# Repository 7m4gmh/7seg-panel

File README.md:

# 7-Segment LED Panel Video Player

A series of tools for playing videos on a custom display panel composed of I2C-connected 7-segment LED modules.

i2cで駆動する自作の7セグメントLEDパネルで、動画を再生するプロジェクト。

---

Note (platform): Developed and tested primarily on Raspberry Pi 3 and Radxa ROCK 5B. It also works on Raspberry Pi 4/5 if I2C is enabled and dependencies are installed (bus numbers/device names may differ).

**macOS Support**: The project includes emulator mode for macOS development and testing. Physical LED panels are automatically simulated with accurate segment rendering and audio synchronization.

注記（プラットフォーム）: 本プロジェクトは主に Raspberry Pi 3 および Radxa ROCK 5B 向けに作成・検証しています。I2C を有効化し依存関係を整えれば Raspberry Pi 4/5 でも動作します（バス番号やデバイス名が異なる場合があります）。

**macOS対応**: 本プロジェクトはmacOSでの開発・テスト用にエミュレータモードを搭載しています。物理的なLEDパネルを自動的にシミュレートし、正確なセグメント描画と音声同期を実現します。

**Languages:**

[**English**](README.en.md) | [**日本語**](README.ja.md) | [**繁體中文**](README.zh-TW.md)

---

**Module Mapping (モジュールマッピング)**

You can define per-module physical mappings in `config.json` to accommodate different wiring or digit order of hardware modules. Use a simple column-reversal flag (`module_column_reverse`) or an explicit logical→physical index map (`module_index_map`). See `docs/module-mapping.md` for details and examples.

ハードウェア毎に桁順や配線が異なる場合、`config.json` でモジュール単位のマッピングを定義できます。簡易的に列方向を反転する `module_column_reverse`（真偽値）を使うか、論理インデックス（左上から行優先）からモジュール内の物理インデックスへ明示的に変換する `module_index_map`（配列）を定義してください。優先順位は `module_index_map` → `module_column_reverse` → 既定順（row-major）です。詳しい書き方とテスト手順は `docs/module-mapping.md` を参照してください。

実機縮退モデルでのデモ動画

[エミュレータでの実行例](https://x.com/HijiriUmemoto/status/2095140881489899897?s=20)

---

## Hardware (KiCad)

- PCB projects live under `hardware/`. See: [hardware/README.md](hardware/README.md)
- Current folders (subject to change):
	- `hardware/7seg-led` — LED panel PCB
	- `hardware/7seg-control` — main controller PCB
	- `hardware/7seg-hat` — Raspberry Pi HAT
	- `hardware/7seg-power` — power board
	- Shared libs: `hardware/lib`
	- Legacy/migration folders may also exist (e.g., `hardware/led-panel`, `controller`, `rpi-hat`, `power`).

---
## Build

Prerequisites
- C++17-capable compiler (g++)
- make
- OpenCV 4 (dev package)
- SDL2 (dev package)
- GStreamer 1.0 (for RTP/HTTP streaming tools)

How to build
- By default, running `make` without arguments shows help and does not build anything.
- Use the grouped targets below as needed.

Common targets

```bash

# Show available targets (default)

make core

# GStreamer-based tools: http-streamer / rtp-player
make gst

# Individual targets
make rtp        # 7seg-rtp-player
# (http-streamerは削除済み)

# Everything
make all

# Cleanup
### macOS Emulator Support
The project includes macOS emulator support for development and testing without physical hardware:
- Automatically detects macOS and uses emulator mode
- Physical LED panel simulation with accurate segment shapes
- Optimized performance with pre-cached layouts
- Audio synchronization for smooth playback

**macOSでのビルド:**
```bash
# OpenCVのインストール
brew install opencv

# ビルド
make core

# エミュレータでのテスト
./7seg-file-player test.mp4 emulator-24x4
```

## Recent changes (video scaling behavior)

This project recently received fixes and improvements to the video scaling modes so behavior is consistent across orientations (horizontal/vertical) and between the real-device and emulator playback paths.

- FIT (default): the entire video is scaled to fit inside the display's physical aspect ratio. Black padding (letterboxing/pillarboxing) will be added on the shorter axis. Internally we compute a display-shaped ROI based on the configured module layout and physical character dimensions, scale the source to fit into that ROI, and pass only the ROI downstream for sampling. This prevents accidental cropping or distortion.

- CROP: the video is center-cropped to match the display's physical aspect ratio while preserving the source aspect ratio. After cropping the ROI is passed downstream without forcing a full W×H canvas resize, so the sampled region keeps correct proportions.

- STRETCH: the video is resized non-uniformly to fill the display-shaped ROI (i.e. aspect ratio is not preserved). This intentionally distorts the video to use the full display area.

These changes make the three modes behave predictably for combinations like horizontal video on vertical displays (FIT will letterbox, CROP will center-crop, STRETCH will distort to fill).

## Debug logging

A new runtime flag is available to enable extra debug output for scaling and ROI calculation.

Usage:
```bash
# Enable debug output
./bin/darwin-arm64/7seg-file-player <video> <config> --fit --debug

# Short form
./bin/darwin-arm64/7seg-file-player <video> <config> --fit -d
```

When enabled the player prints per-frame messages like:

- [FIT] source_aspect=... display_aspect=... roi=(x,y,w,h) dst=(w,h)
- [STRETCH] source_aspect=... display_aspect=... roi=(x,y,w,h)

The debug flag is off by default so normal runs are quiet.

## Notes for reviewers / maintainers

- The playback code now avoids forcing a W×H resize for FIT/CROP/STRETCH; we pass an appropriately-shaped ROI to the sampling logic so `frame_to_grid` sees the correct proportions.
- Debug prints are gated by the `--debug`/`-d` switch.
- Some small cleanups were applied (unused variables removed, minor refactor of logging points).

Tip
- For streaming, we recommend the net player with OBS via FLV/TCP:
	- [README.en.md](README.en.md) → "Send directly from OBS (FLV/TCP)"
	- [README.ja.md](README.ja.md) → 「OBSから直接送信（FLV/TCP）」
	- [README.zh-TW.md](README.zh-TW.md) → 「從 OBS 直接傳送（FLV/TCP）」
- Alternatively, the RTP player is available. See usage and sender examples:
	- [README.en.md](README.en.md) → "RTP Player (Recommended)"
	- [README.ja.md](README.ja.md) → 「RTPプレイヤー（推奨）」
	- [README.zh-TW.md](README.zh-TW.md) → 「RTP 播放器（建議）」
- macOS camera sender script included: `send_rtp_cam_gst.sh`
 - For browser-based control and uploads, use the HTTP player/streamer. See:
	 - [README.en.md](README.en.md) → "HTTP Player"
	 - [README.ja.md](README.ja.md) → 「HTTPプレイヤー」
	 - [README.zh-TW.md](README.zh-TW.md) → 「HTTP 播放器」
 - To play a local video file quickly, use the File Player. See:
	 - [README.en.md](README.en.md) → "File Player"
	 - [README.ja.md](README.ja.md) → 「ファイルプレイヤー」
	 - [README.zh-TW.md](README.zh-TW.md) → 「檔案播放器」

- **macOS Emulator**: For testing and development on macOS without physical hardware. See:
	 - [README.emulator.md](README.emulator.md) → "7-Segment LED Panel Emulator"
	 - 物理的なLEDパネルの正確なシミュレーション
	 - 動画ファイルからの再生と音声同期

- Tetris on the LED panel (Python):
	- [README.tetris.en.md](README.tetris.en.md)
	- [README.tetris.md](README.tetris.md)（日本語）
	- [README.tetris.zh-TW.md](README.tetris.zh-TW.md)

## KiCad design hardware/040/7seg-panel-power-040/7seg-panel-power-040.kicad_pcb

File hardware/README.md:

# Hardware projects

基板ごとに独立した KiCad プロジェクトとして、世代・構成別のフォルダに配置しています。

This folder contains independent KiCad projects grouped by hardware generation and configuration.

## Directory structure

### 040 series

- `040/`
    - `7seg-panel-control-040/`
    - `7seg-panel-control-040-dual/`
    - `7seg-panel-control-040-single/`
    - `7seg-panel-control-04in/`
    - `7seg-panel-display-040-dual/`
    - `7seg-panel-display-040-dual-24x16/`
    - `7seg-panel-expand-040/`
    - `7seg-panel-power-040/`
    - `7seg-panel-single-04in/`
- `040-sparse/`
    - `7seg-panel-040-display-dual-wide/`
    - `7seg-panel-040-dual-combined-sparse/`

### 056 series

- `056/`
    - `7seg-control/`
    - `7seg-led/`
    - `7seg-panel-4digit/`
    - `7seg-panel-single-digit/`
    - `7seg-power/`
- `056-sparse/`
    - `7-seg-panel-0560dual combined-sparse/`
    - `7seg-panel-056-display-wide/`
    - `7seg-panel-056-single-combined-sparse/`
- `056-HT1635D/`
    - `056-ht1635d-driver/`

### Raspberry Pi HAT

- `7seg-hat/`
    - `7seg-hat.kicad_pro`, `7seg-hat.kicad_sch`, `7seg-hat.kicad_pcb`
    - `7seg-hat-backups/`
    - `20250729-7seg-led-panel-hat-backups/`
    - `20250815-7seg-led-panel-hat-backups/`
    - `bom/`
    - `production/`

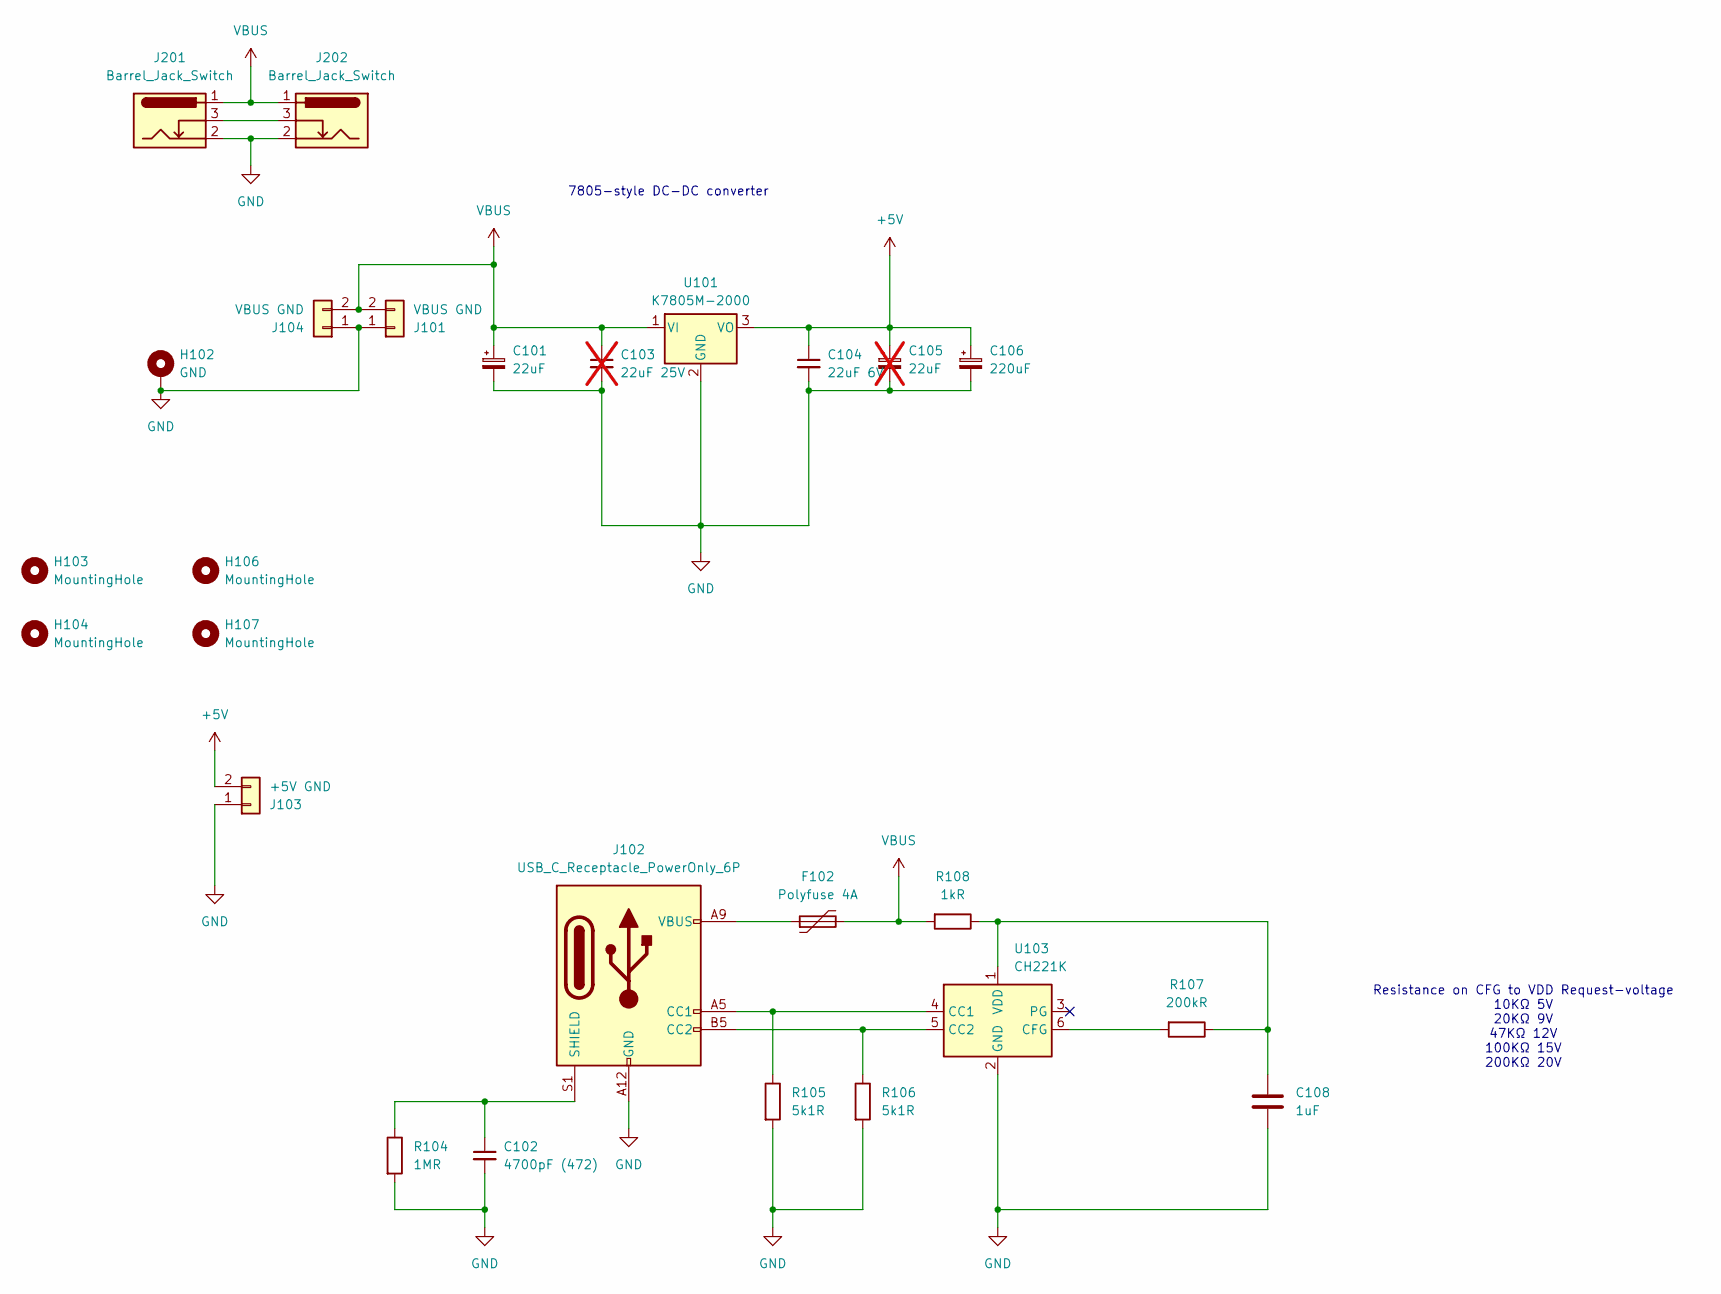
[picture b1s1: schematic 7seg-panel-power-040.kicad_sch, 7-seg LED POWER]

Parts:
C101: 22uF; CP_EIA-3528-21_Kemet-B
C102: 4700pF (472); C_0805_2012Metric_Pad1.18x1.45mm_HandSolder
C103: 22uF 25V; C_0603_1608Metric_Pad1.08x0.95mm_HandSolder; not fitted
C104: 22uF 6V; C_0603_1608Metric_Pad1.08x0.95mm_HandSolder
C105: 22uF; CP_EIA-3528-21_Kemet-B; not fitted
C106: 220uF; CP_Radial_D6.3mm_P2.50mm
C108: 1uF; C_0805_2012Metric_Pad1.18x1.45mm_HandSolder
F102: Polyfuse 4A; Fuse_2920_7451Metric_Pad2.10x5.45mm_HandSolder
H102: GND; MountingHole_3.2mm_M3_DIN965_Pad
H103, H104, H106, H107: MountingHole; MountingHole_3.2mm_M3
J101, J104: VBUS GND; Generic_XH_S2B-XH-A-1_1x02_P2.50mm_Horizontal
J102: USB_C_Receptacle_PowerOnly_6P; USB_C_Receptacle_HRO_TYPE-C-31-M-17
J103: +5V GND; Generic_XH_S2B-XH-A-1_1x02_P2.50mm_Horizontal
J201, J202: Barrel_Jack_Switch; BarrelJack_Singatron_2DC-0415D200-SMT_Horizontal
R104: 1MR; R_0805_2012Metric_Pad1.20x1.40mm_HandSolder
R105, R106: 5k1R; R_0805_2012Metric_Pad1.20x1.40mm_HandSolder
R107: 200kR; R_0805_2012Metric_Pad1.20x1.40mm_HandSolder
R108: 1kR; R_1210_3225Metric_Pad1.30x2.65mm_HandSolder
U101: K7805M-2000; TO-220-3_Vertical
U103: CH221K; TSOT-23-6_HandSoldering

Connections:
+5V: C104.1, C105.1, C106.1, J103.2, U101.3 (VO)
GND: C101.2, C102.2, C103.2, C104.2, C105.2, C106.2, C108.2, H102.1 (MP_1), J101.1, J102.A12 (GND), J102.B12 (GND), J103.1, J104.1, J201.2, J202.2, R104.2, R105.2, R106.2, U101.2 (GND), U103.2 (GND)
unnamed: F102.1, J102.A9 (VBUS), J102.B9 (VBUS)
unnamed: J102.A5 (CC1), R105.1, U103.4 (CC1)
unnamed: J102.B5 (CC2), R106.1, U103.5 (CC2)
unnamed: C102.1, J102.S1 (SHIELD), R104.1
unnamed: J201.3, J202.3
unnamed: R107.2, U103.6 (CFG)
unnamed: C108.1, R107.1, R108.1, U103.1 (VDD)
VBUS: C101.1, C103.1, F102.2, J101.2, J104.2, J201.1, J202.1, R108.2, U101.1 (VI)

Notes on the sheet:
7805-style DC-DC converter
Resistance on CFG to VDD Request-voltage 10KΩ 5V 20KΩ 9V 47KΩ 12V 100KΩ 15V 200KΩ 20V

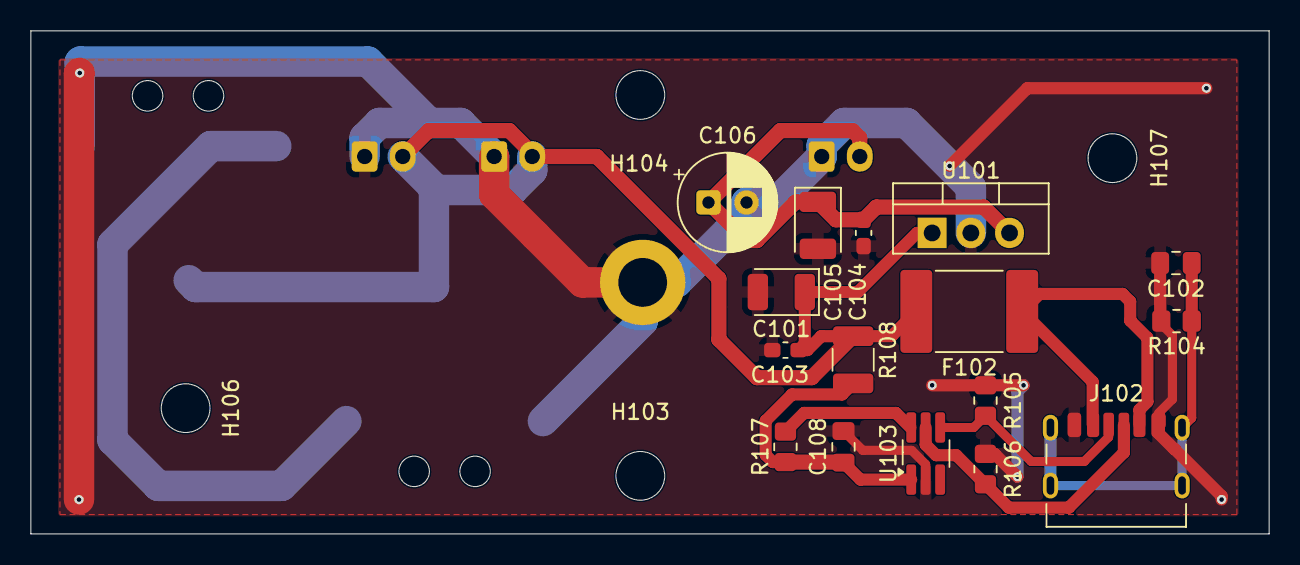
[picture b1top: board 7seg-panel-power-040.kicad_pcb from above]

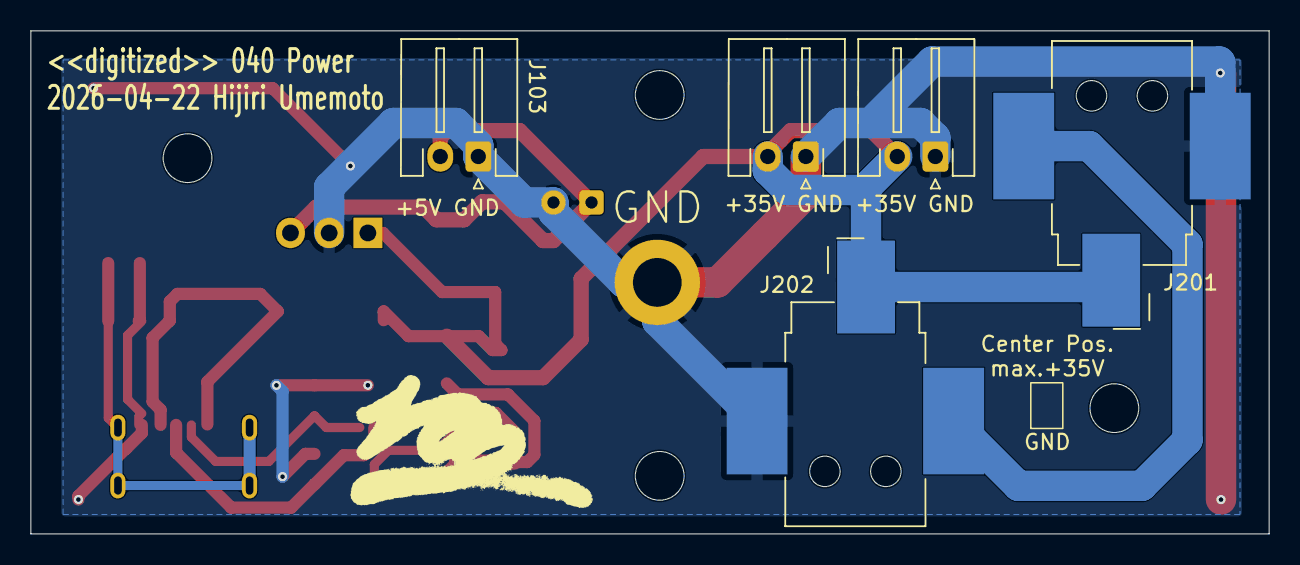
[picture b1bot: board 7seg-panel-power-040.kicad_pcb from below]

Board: 2 copper layers, 81.3 x 33.0 mm, 26 parts (5 on the bottom side), 10 nets.

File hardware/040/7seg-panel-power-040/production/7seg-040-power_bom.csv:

Designator,Footprint,Quantity,Value,LCSC Part #
C101,CP_EIA-3528-21_Kemet-B,1,22uF,
C102,0805,1,4700pF (472),
C104,0603,1,22uF 6V,
C106,CP_Radial_D6.3mm_P2.50mm,1,220uF,
C108,0805,1,1uF,
F102,2920,1,Polyfuse 4A,
"J101, J104",Generic_XH_S2B-XH-A-1_1x02_P2.50mm_Horizontal,2,+35V GND,
J102,USB_C_Receptacle_HRO_TYPE-C-31-M-17,1,USB_C_Receptacle_PowerOnly_6P,
J103,Generic_XH_S2B-XH-A-1_1x02_P2.50mm_Horizontal,1,+5V GND,
"J201, J202",BarrelJack_Singatron_2DC-0415D200-SMT_Horizontal,2,Barrel_Jack_Switch,
R104,0805,1,1MR,
"R105, R106",0805,2,5k1R,
R107,0805,1,200kR,
R108,1210,1,1kR,
U101,TO-220-3_Vertical,1,K7805M-2000,
U103,TSOT-23-6_HandSoldering,1,CH221K,

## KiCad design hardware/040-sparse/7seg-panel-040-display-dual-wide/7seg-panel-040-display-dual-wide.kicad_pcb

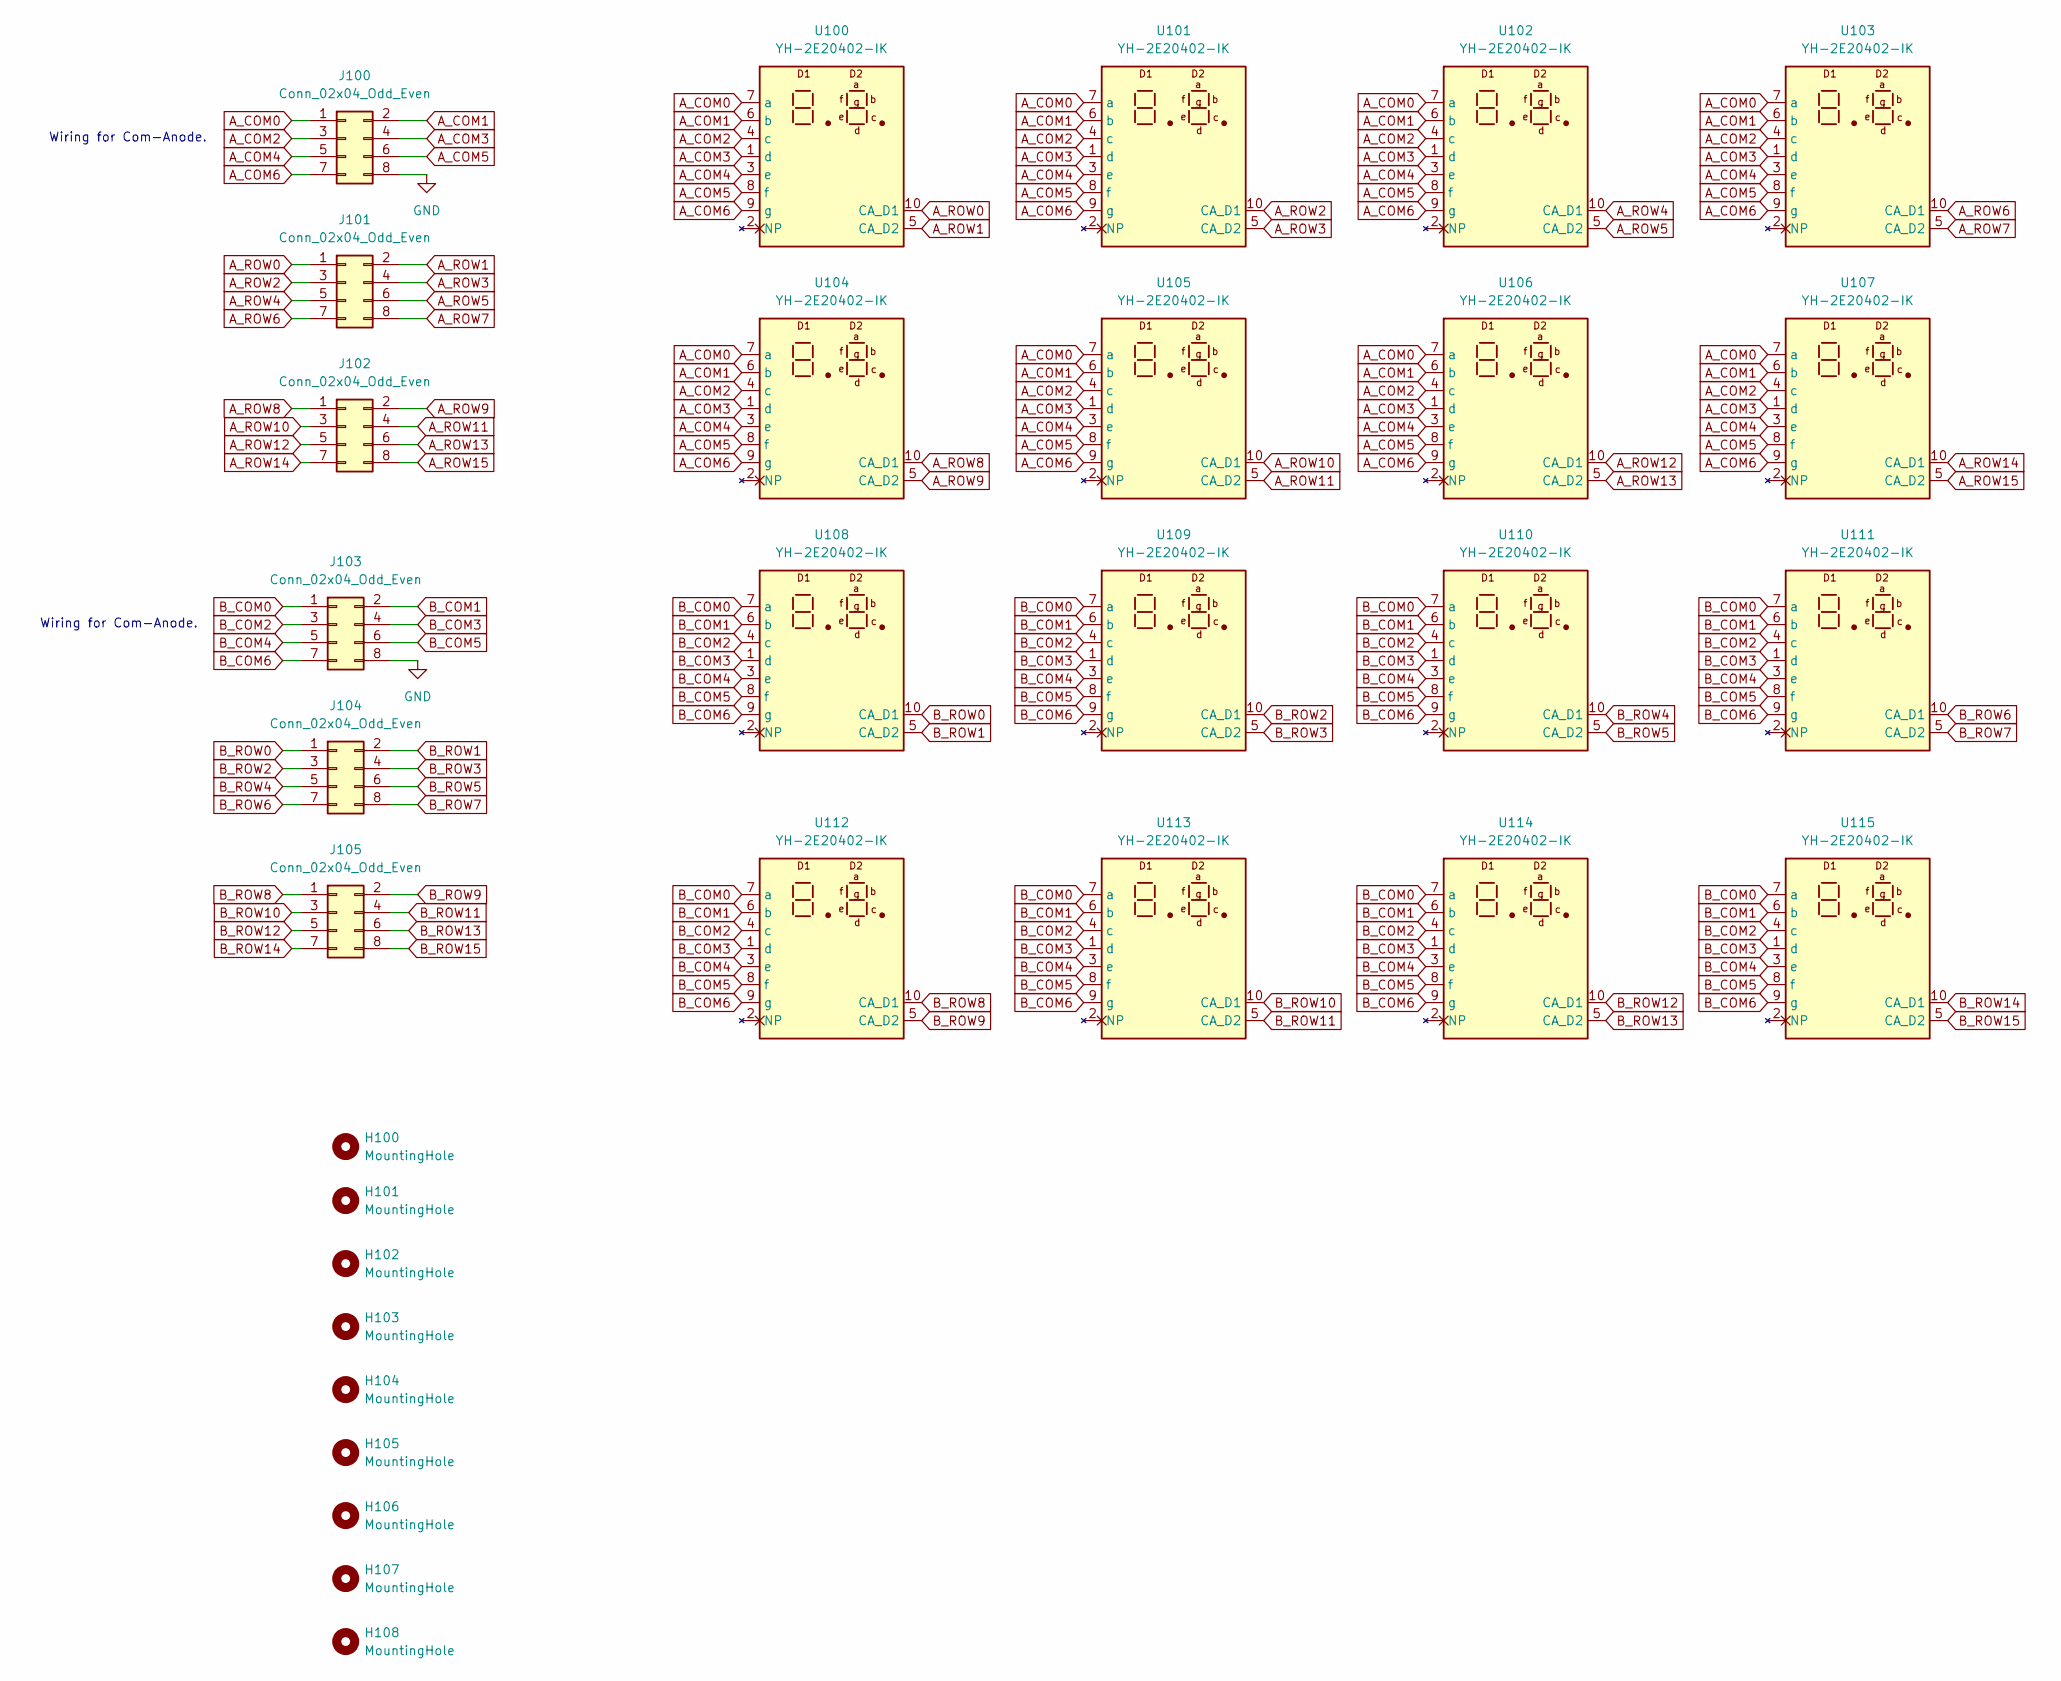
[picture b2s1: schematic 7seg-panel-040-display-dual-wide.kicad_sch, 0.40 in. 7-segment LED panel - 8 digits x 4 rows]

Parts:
H100, H101, H102, H103, H104, H105, H106, H107, H108: MountingHole; MountingHole_3.2mm_M3
J100, J101, J102, J103, J104, J105: Conn_02x04_Odd_Even; PinHeader_2x04_P2.54mm_Vertical
U100, U101, U102, U103, U104, U105, U106, U107, U108, U109, U110, U111, U112, U113, U114, U115: YH-2E20402-IK; YH-2E20402-12P

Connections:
A_COM0: J100.1, U100.7 (a), U101.7 (a), U102.7 (a), U103.7 (a), U104.7 (a), U105.7 (a), U106.7 (a), U107.7 (a)
A_COM1: J100.2, U100.6 (b), U101.6 (b), U102.6 (b), U103.6 (b), U104.6 (b), U105.6 (b), U106.6 (b), U107.6 (b)
A_COM2: J100.3, U100.4 (c), U101.4 (c), U102.4 (c), U103.4 (c), U104.4 (c), U105.4 (c), U106.4 (c), U107.4 (c)
A_COM3: J100.4, U100.1 (d), U101.1 (d), U102.1 (d), U103.1 (d), U104.1 (d), U105.1 (d), U106.1 (d), U107.1 (d)
A_COM4: J100.5, U100.3 (e), U101.3 (e), U102.3 (e), U103.3 (e), U104.3 (e), U105.3 (e), U106.3 (e), U107.3 (e)
A_COM5: J100.6, U100.8 (f), U101.8 (f), U102.8 (f), U103.8 (f), U104.8 (f), U105.8 (f), U106.8 (f), U107.8 (f)
A_COM6: J100.7, U100.9 (g), U101.9 (g), U102.9 (g), U103.9 (g), U104.9 (g), U105.9 (g), U106.9 (g), U107.9 (g)
A_ROW0: J101.1, U100.10 (CA_D1)
A_ROW1: J101.2, U100.5 (CA_D2)
A_ROW2: J101.3, U101.10 (CA_D1)
A_ROW3: J101.4, U101.5 (CA_D2)
A_ROW4: J101.5, U102.10 (CA_D1)
A_ROW5: J101.6, U102.5 (CA_D2)
A_ROW6: J101.7, U103.10 (CA_D1)
A_ROW7: J101.8, U103.5 (CA_D2)
A_ROW8: J102.1, U104.10 (CA_D1)
A_ROW9: J102.2, U104.5 (CA_D2)
A_ROW10: J102.3, U105.10 (CA_D1)
A_ROW11: J102.4, U105.5 (CA_D2)
A_ROW12: J102.5, U106.10 (CA_D1)
A_ROW13: J102.6, U106.5 (CA_D2)
A_ROW14: J102.7, U107.10 (CA_D1)
A_ROW15: J102.8, U107.5 (CA_D2)
B_COM0: J103.1, U108.7 (a), U109.7 (a), U110.7 (a), U111.7 (a), U112.7 (a), U113.7 (a), U114.7 (a), U115.7 (a)
B_COM1: J103.2, U108.6 (b), U109.6 (b), U110.6 (b), U111.6 (b), U112.6 (b), U113.6 (b), U114.6 (b), U115.6 (b)
B_COM2: J103.3, U108.4 (c), U109.4 (c), U110.4 (c), U111.4 (c), U112.4 (c), U113.4 (c), U114.4 (c), U115.4 (c)
B_COM3: J103.4, U108.1 (d), U109.1 (d), U110.1 (d), U111.1 (d), U112.1 (d), U113.1 (d), U114.1 (d), U115.1 (d)
B_COM4: J103.5, U108.3 (e), U109.3 (e), U110.3 (e), U111.3 (e), U112.3 (e), U113.3 (e), U114.3 (e), U115.3 (e)
B_COM5: J103.6, U108.8 (f), U109.8 (f), U110.8 (f), U111.8 (f), U112.8 (f), U113.8 (f), U114.8 (f), U115.8 (f)
B_COM6: J103.7, U108.9 (g), U109.9 (g), U110.9 (g), U111.9 (g), U112.9 (g), U113.9 (g), U114.9 (g), U115.9 (g)
B_ROW0: J104.1, U108.10 (CA_D1)
B_ROW1: J104.2, U108.5 (CA_D2)
B_ROW2: J104.3, U109.10 (CA_D1)
B_ROW3: J104.4, U109.5 (CA_D2)
B_ROW4: J104.5, U110.10 (CA_D1)
B_ROW5: J104.6, U110.5 (CA_D2)
B_ROW6: J104.7, U111.10 (CA_D1)
B_ROW7: J104.8, U111.5 (CA_D2)
B_ROW8: J105.1, U112.10 (CA_D1)
B_ROW9: J105.2, U112.5 (CA_D2)
B_ROW10: J105.3, U113.10 (CA_D1)
B_ROW11: J105.4, U113.5 (CA_D2)
B_ROW12: J105.5, U114.10 (CA_D1)
B_ROW13: J105.6, U114.5 (CA_D2)
B_ROW14: J105.7, U115.10 (CA_D1)
B_ROW15: J105.8, U115.5 (CA_D2)
GND: J100.8, J103.8

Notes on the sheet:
Wiring for Com-Anode.

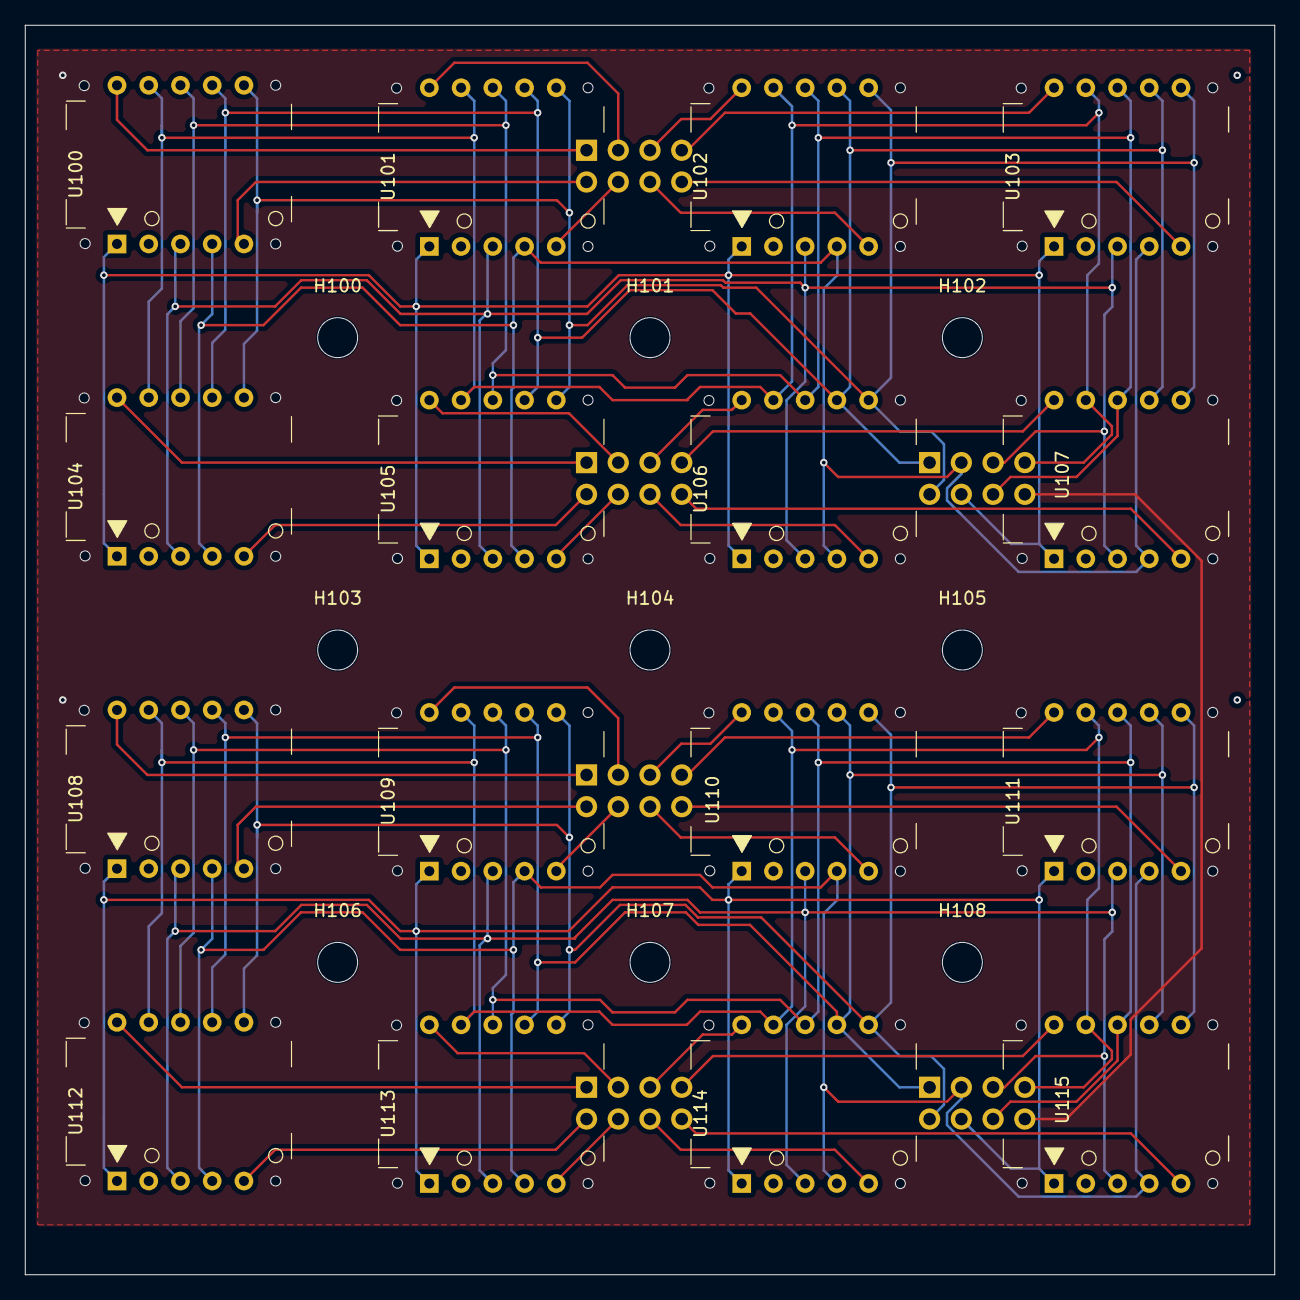
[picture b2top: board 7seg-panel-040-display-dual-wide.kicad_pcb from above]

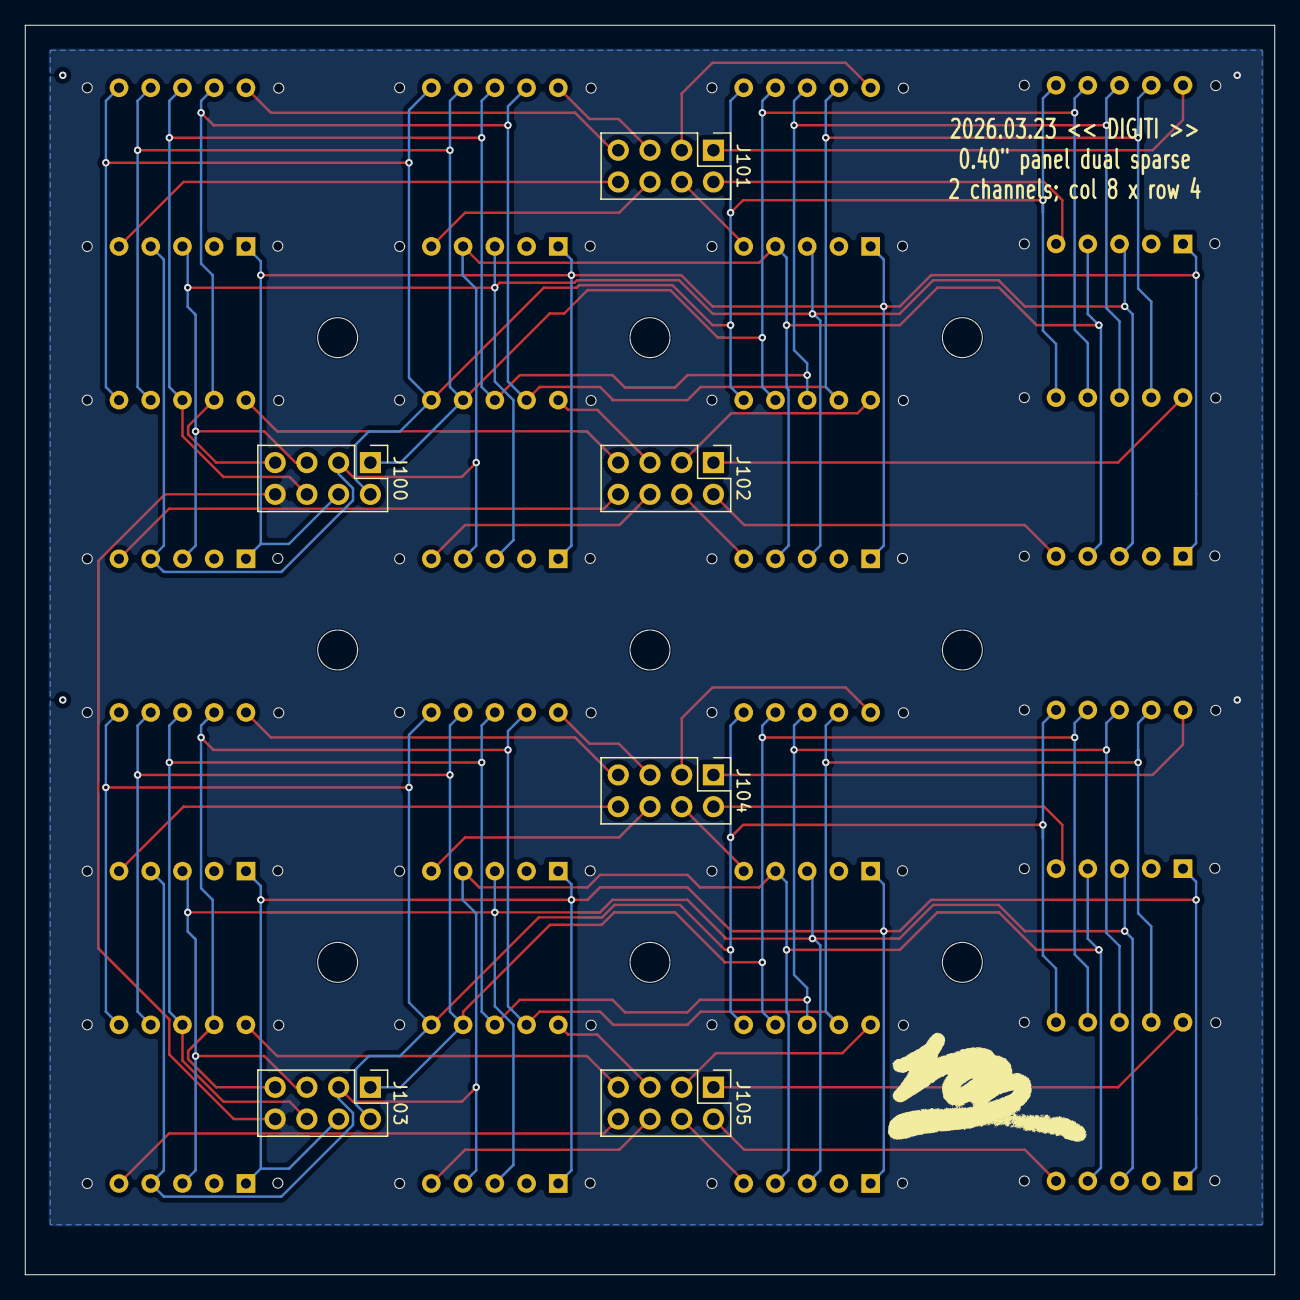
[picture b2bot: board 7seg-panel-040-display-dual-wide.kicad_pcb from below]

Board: 2 copper layers, 100.0 x 100.0 mm, 31 parts (6 on the bottom side), 47 nets.

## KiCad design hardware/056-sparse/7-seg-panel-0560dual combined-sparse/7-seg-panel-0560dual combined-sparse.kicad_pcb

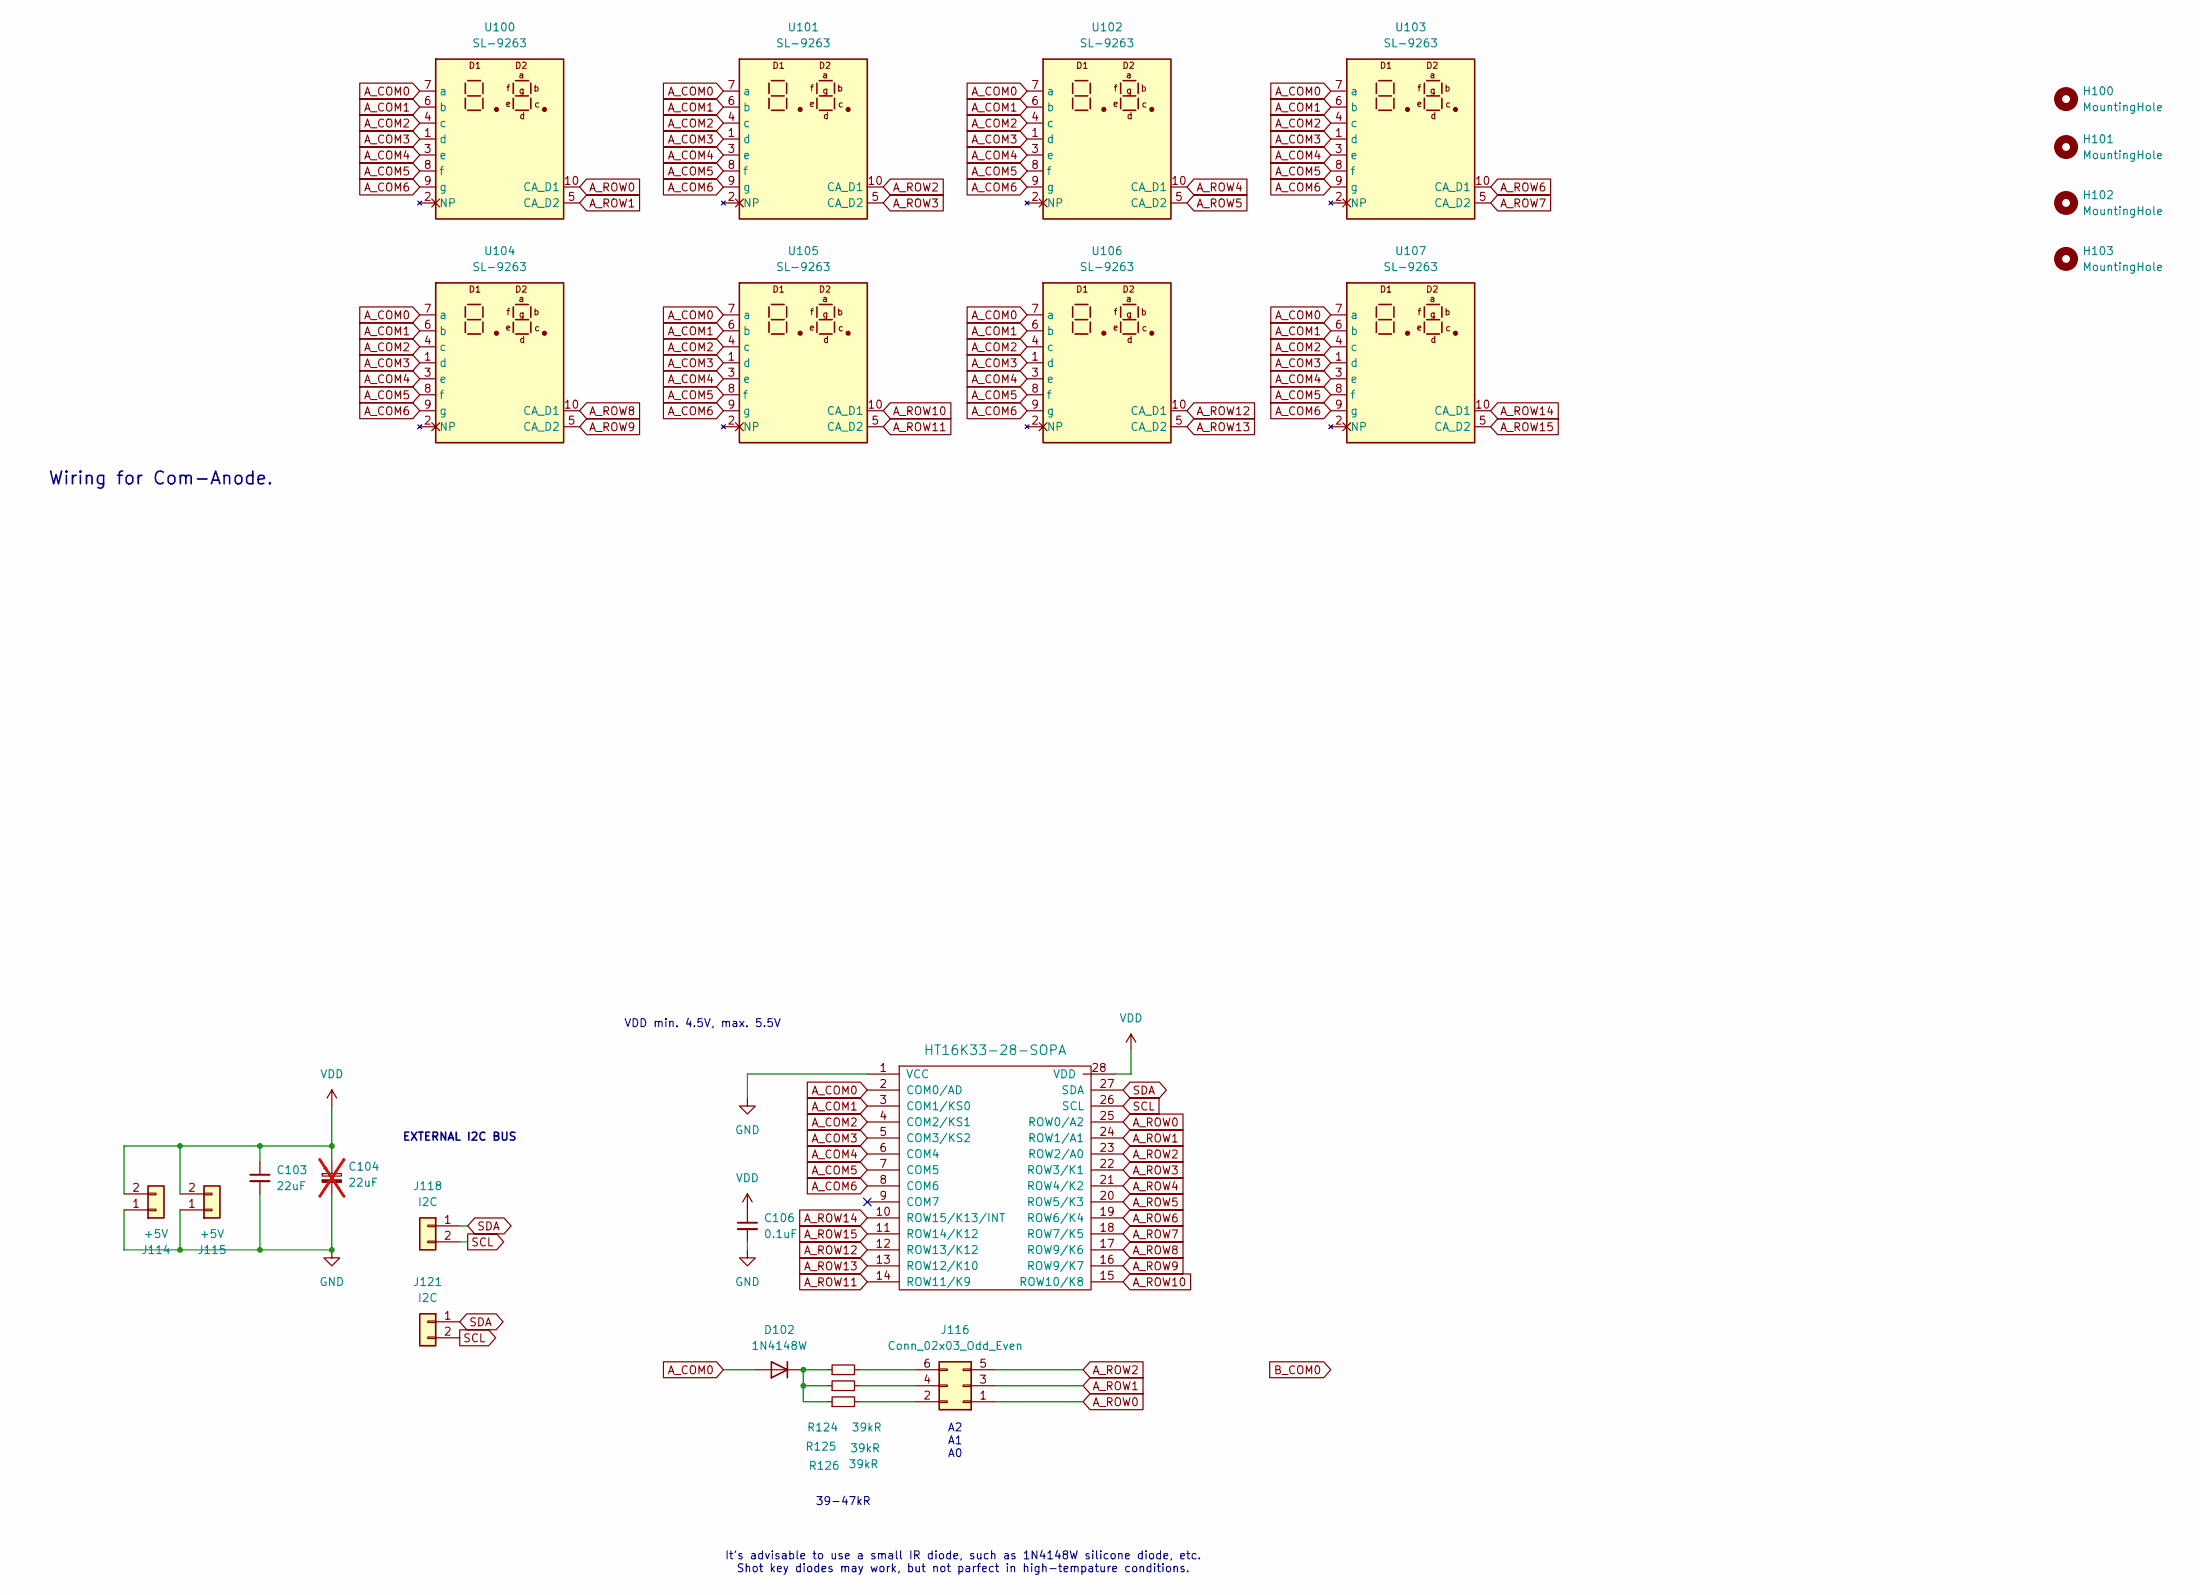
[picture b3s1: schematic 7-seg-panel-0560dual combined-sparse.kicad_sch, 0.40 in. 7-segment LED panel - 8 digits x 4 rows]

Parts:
C103: 22uF; C_0603_1608Metric
C104: 22uF; CP_EIA-3528-21_Kemet-B_HandSolder; not fitted
C106: 0.1uF; C_0603_1608Metric_Pad1.08x0.95mm_HandSolder
D102: 1N4148W; D_SOD-123
H100, H101, H102, H103: MountingHole; MountingHole_3.2mm_M3
J114, J115: +5V; JST_XH_B2B-XH-AM_1x02_P2.50mm_Vertical
J116: Conn_02x03_Odd_Even; PinHeader_2x03_P2.54mm_Vertical
J118, J121: I2C; JST_XH_B2B-XH-AM_1x02_P2.50mm_Vertical
R124, R125, R126: 39kR; R_0603_1608Metric_Pad0.98x0.95mm_HandSolder
U100, U101, U102, U103, U104, U105, U106, U107: SL-9263; DA56-11CGKWA
U116: HT16K33-28-SOPA; SOP-28_8.4x18.16mm_P1.27mm

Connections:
A_COM0: D102.2 (A), U100.7 (a), U101.7 (a), U102.7 (a), U103.7 (a), U104.7 (a), U105.7 (a), U106.7 (a), U107.7 (a), U116.2 (COM0/AD)
A_COM1: U100.6 (b), U101.6 (b), U102.6 (b), U103.6 (b), U104.6 (b), U105.6 (b), U106.6 (b), U107.6 (b), U116.3 (COM1/KS0)
A_COM2: U100.4 (c), U101.4 (c), U102.4 (c), U103.4 (c), U104.4 (c), U105.4 (c), U106.4 (c), U107.4 (c), U116.4 (COM2/KS1)
A_COM3: U100.1 (d), U101.1 (d), U102.1 (d), U103.1 (d), U104.1 (d), U105.1 (d), U106.1 (d), U107.1 (d), U116.5 (COM3/KS2)
A_COM4: U100.3 (e), U101.3 (e), U102.3 (e), U103.3 (e), U104.3 (e), U105.3 (e), U106.3 (e), U107.3 (e), U116.6 (COM4)
A_COM5: U100.8 (f), U101.8 (f), U102.8 (f), U103.8 (f), U104.8 (f), U105.8 (f), U106.8 (f), U107.8 (f), U116.7 (COM5)
A_COM6: U100.9 (g), U101.9 (g), U102.9 (g), U103.9 (g), U104.9 (g), U105.9 (g), U106.9 (g), U107.9 (g), U116.8 (COM6)
A_ROW0: J116.1, U100.10 (CA_D1), U116.25 (ROW0/A2)
A_ROW1: J116.3, U100.5 (CA_D2), U116.24 (ROW1/A1)
A_ROW2: J116.5, U101.10 (CA_D1), U116.23 (ROW2/A0)
A_ROW3: U101.5 (CA_D2), U116.22 (ROW3/K1)
A_ROW4: U102.10 (CA_D1), U116.21 (ROW4/K2)
A_ROW5: U102.5 (CA_D2), U116.20 (ROW5/K3)
A_ROW6: U103.10 (CA_D1), U116.19 (ROW6/K4)
A_ROW7: U103.5 (CA_D2), U116.18 (ROW7/K5)
A_ROW8: U104.10 (CA_D1), U116.17 (ROW9/K6)
A_ROW9: U104.5 (CA_D2), U116.16 (ROW9/K7)
A_ROW10: U105.10 (CA_D1), U116.15 (ROW10/K8)
A_ROW11: U105.5 (CA_D2), U116.14 (ROW11/K9)
A_ROW12: U106.10 (CA_D1), U116.12 (ROW13/K12)
A_ROW13: U106.5 (CA_D2), U116.13 (ROW12/K10)
A_ROW14: U107.10 (CA_D1), U116.10 (ROW15/K13/INT)
A_ROW15: U107.5 (CA_D2), U116.11 (ROW14/K12)
GND: C103.2, C104.2, C106.2, J114.1, J115.1, U116.1 (VCC)
unnamed: D102.1 (K), R124.1, R125.1, R126.1
unnamed: J116.2, R126.2
unnamed: J116.4, R125.2
unnamed: J116.6, R124.2
SCL: J118.2, J121.2, U116.26 (SCL)
SDA: J118.1, J121.1, U116.27 (SDA)
VDD: C103.1, C104.1, C106.1, J114.2, J115.2, U116.28 (VDD)

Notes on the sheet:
VDD min. 4.5V, max. 5.5V
It's advisable to use a small IR diode, such as 1N4148W silicone diode, etc. Shot key diodes may work, but not parfect in high-tempature conditions.
Wiring for Com-Anode.
EXTERNAL I2C BUS
39-47kR
A2 A1 A0
